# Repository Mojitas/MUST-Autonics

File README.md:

# Main repository for: MUST-Autonics 

## Sub-project VT1: Testbench

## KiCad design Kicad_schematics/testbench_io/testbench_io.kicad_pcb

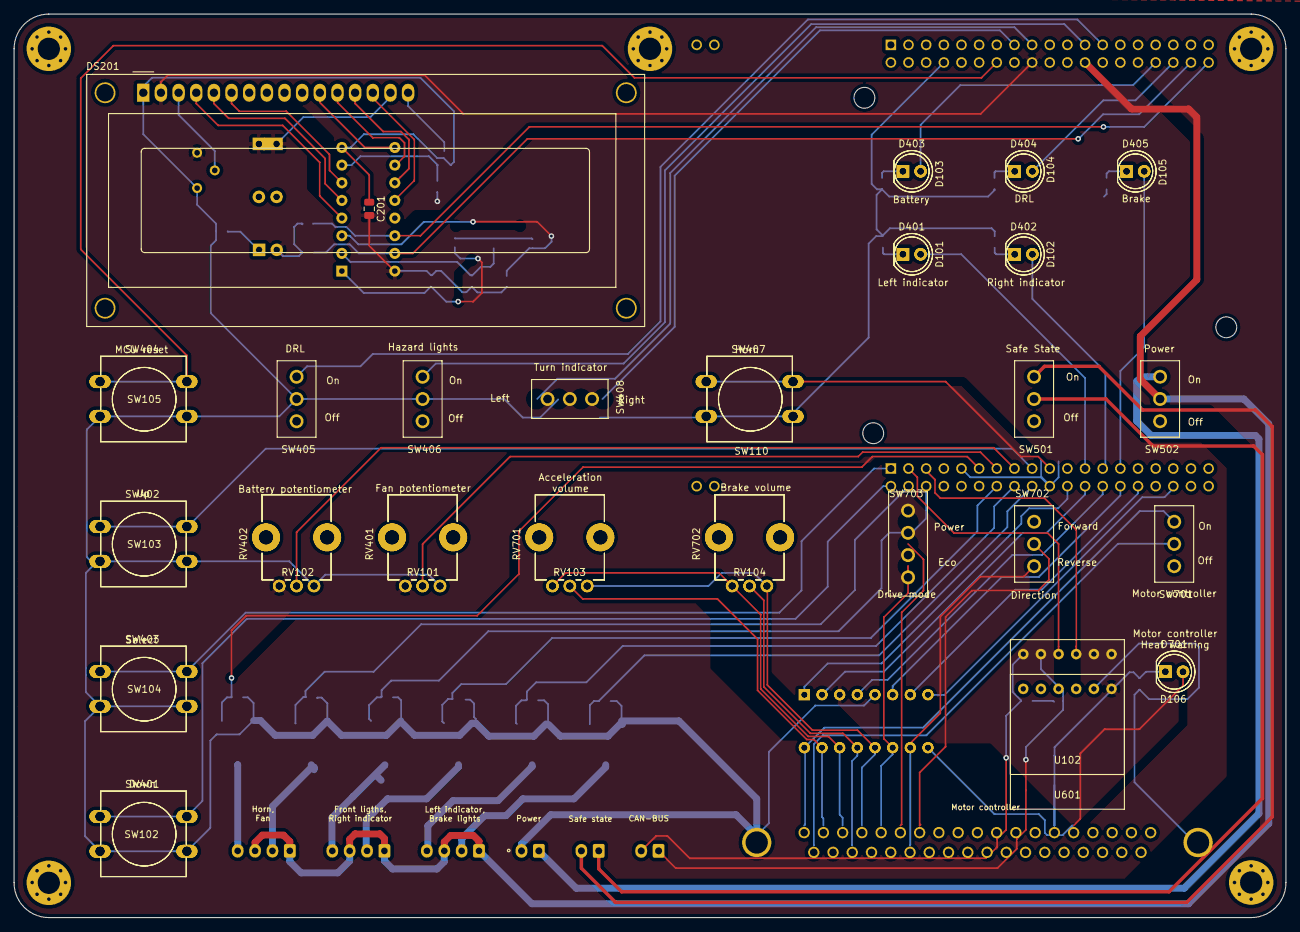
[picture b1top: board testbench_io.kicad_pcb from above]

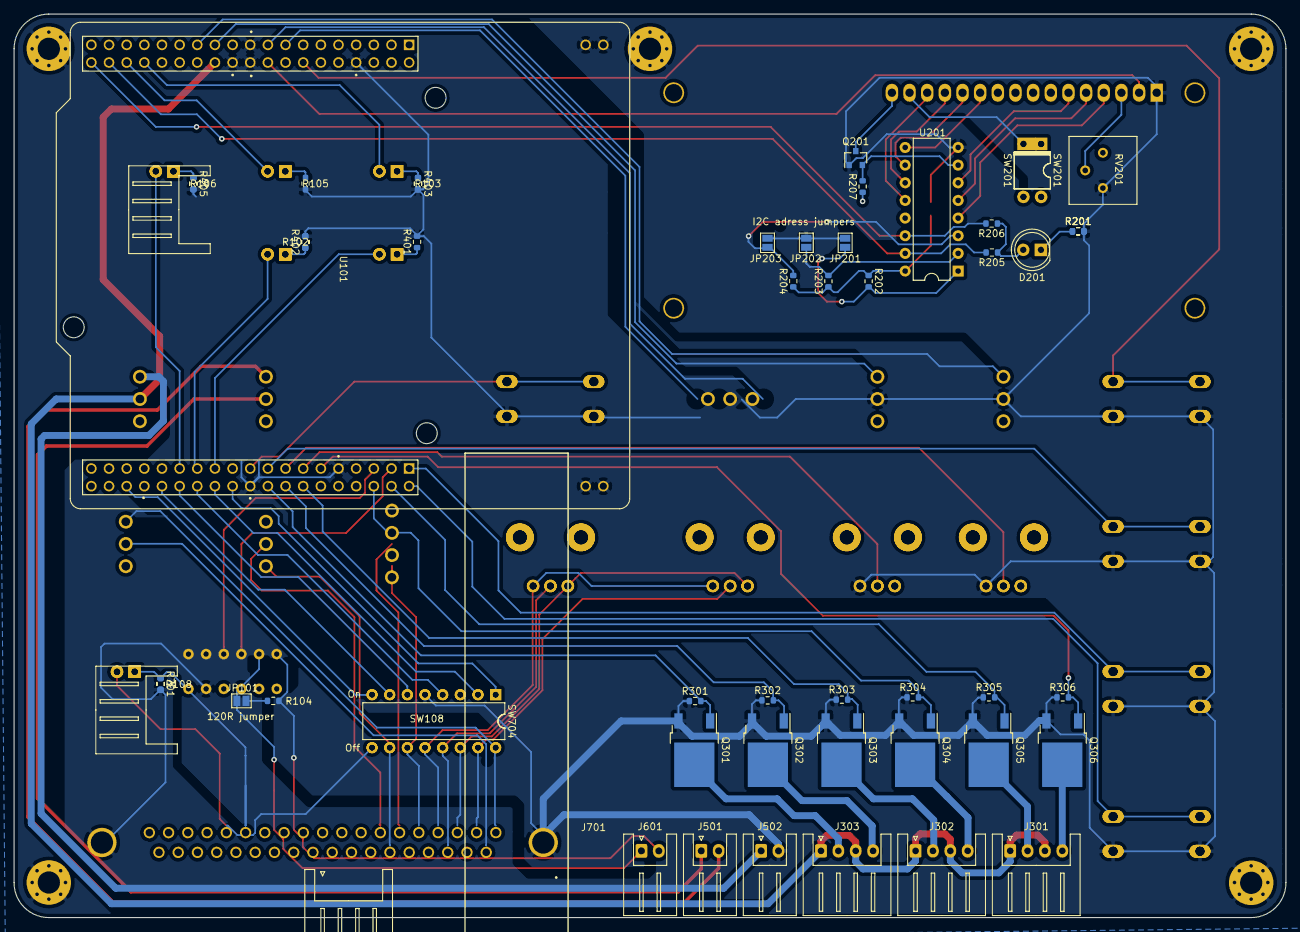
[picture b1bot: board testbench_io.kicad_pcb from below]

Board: 2 copper layers, 183.0 x 130.0 mm, 98 parts (51 on the bottom side), 87 nets.

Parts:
C201: 100n; C_0805_2012Metric
D101, D102, D103, D104, D105, D106, D201, D401, D402, D403, D404, D405, D701: LED; LED_D5.0mm
DS201: WC1602A
H101, H102, H103, H104, H105: MountingHole_Pad; MountingHole_3.2mm_M3_Pad_Via
J301, J302, J303: Conn_01x04; JST_XH_S4B-XH-A_1x04_P2.50mm_Horizontal
J501, J502, J601: Conn_01x02; JST_XH_S2B-XH-A_1x02_P2.50mm_Horizontal
J701: DB37_Male_MountingHoles; Wurth_Dsub_37_angled_male_8.08mm
JP101, JP201, JP202, JP203: SolderJumper_2_Open; SolderJumper-2_P1.3mm_Open_Pad1.0x1.5mm
Q201: 2N3904; SOT-23
Q301, Q302, Q303, Q304, Q305, Q306: IPD50R380CE; TO-252-2
R102, R103, R105, R106, R108, R305, R306, R401, R402, R403, R405, R701: R_Small; R_0603_1608Metric
R104: 120; R_0603_1608Metric
R201, R201#2: 1k; R_0603_1608Metric
R202, R203, R204, R301, R302, R303: 10k; R_0603_1608Metric
R205, R206, R207: 4.7; R_0603_1608Metric
R304: 100k; R_0603_1608Metric
RV101, RV102, RV103, RV104, RV401, RV402, RV701, RV702: R_POT; Potentiometer_Bourns_PTV09A-1_Single_Vertical
RV201: 10k; Potentiometer_Bourns_3386P_Vertical
SW102, SW103, SW104, SW105, SW110, SW401, SW402, SW403, SW404, SW407: SW_Push; SW_PUSH-12mm
SW108, SW704: SW_DIP_x08; DIP-16_W7.62mm
SW201: SW_DIP_x01; DIP-4_W7.62mm
SW201#2: SW_DIP_x01; Vishay_HVM-DIP-3_W7.62mm
SW405, SW406, SW501, SW502, SW701, SW702, SW703: SW_SPST; MFP120
SW408: SW_DPDT_x2; MFP130
U101: NUCLEO64-F476RG; MODULE_NUCLEO-F476RG
U102, U601: CJMCU_MCP2551; CJMCU_2551
U201: PCF8574AN; DIP-16_W7.62mm

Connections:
/Acc_vol: SW108.2, SW704.2, U101.62
/Battery_LED: D103.2, D403.2, U101.32
/Battery_pot: RV102.2, RV402.2, U101.53
/Brake_LED: D105.2, D405.2, U101.65
/Brake_acti: Q301.1, R301.2, U101.54
/Brake_vol: SW108.4, SW704.4, U101.64
/CAN/CAN_N: J601.1, R701.1, U601.6
/CAN/CAN_P: J601.2, R701.2, U601.5
/CRX: U101.41, U102.4, U601.4
/CTX: U101.43, U102.3, U601.3
/DRL_LED: D104.2, D404.2, U101.34
/DRL_sw: SW405.1, U101.25
/Down: SW102.1, SW401.1, U101.40
/F-R_sw: SW108.7, SW704.7, U101.68
/Fan_pot: RV101.2, RV401.2, U101.51
/Fan_pwm: Q305.1, R305.2, U101.42
/Front_acti: Q304.1, R304.2, U101.44
/HL_sw: SW406.1, U101.23
/Horn_acti: Q306.1, R306.2, U101.49
/Horn_sw: SW110.1, SW407.1, U101.57
/LCD_I2C/DB4: DS201.11, U201.9
/LCD_I2C/DB5: DS201.12, U201.10
/LCD_I2C/DB6: DS201.13, U201.11
/LCD_I2C/DB7: DS201.14, U201.12
/LCD_I2C/E: DS201.6, U201.6
/LCD_I2C/LED_(+): DS201.15, SW201.2, SW201#2.2
/LCD_I2C/LED_(-): DS201.16, Q201.3
/LCD_I2C/RS: DS201.4, U201.4
/LCD_I2C/RW: DS201.5, U201.5
/LCD_I2C/pot_brightness: DS201.3, RV201.2
/Left_LED: D101.2, D401.2, U101.61
/Left_acti: Q302.1, R302.2, U101.52
/Left_sw: SW703.1, U101.17
/MC_LED: SW108.8, SW704.8, U101.72
/MC_sw: SW108.1, SW704.1, U101.60
/Motor_controller/TRM_01: J701.1, SW701.1, SW704.16
/Motor_controller/TRM_02: J701.2, RV701.2, SW704.15
/Motor_controller/TRM_05: J701.5, SW704.11
/Motor_controller/TRM_14: D701.1, J701.14
/Motor_controller/TRM_15: D701.2, J701.15, SW704.9
/Motor_controller/TRM_20: J701.20, SW701.2
/Motor_controller/TRM_22: J701.22, RV702.2, SW704.13
/Motor_controller/TRM_25: J701.25, SW704.10
/P-E_sw: SW108.6, SW704.6, U101.66
/Reset: SW105.1, SW404.1, U101.14
/Right_LED: D102.2, D402.2, U101.63
/Right_acti: Q303.1, R303.2, U101.50
/Right_sw: SW703.3, U101.15
/SCL: R206.2, U101.38, U201.14
/SDA: R205.2, U101.36, U201.15
/Select: SW104.1, SW403.1, U101.39
/Solar_lights/Brake_lights_VSS: J303.2, Q301.2
/Solar_lights/Fan_VSS: J301.2, Q305.2
/Solar_lights/Front_lights_VSS: J302.4, Q304.2
/Solar_lights/Horn_VSS: J301.4, Q306.2
/Solar_lights/Left_indicator_VSS: J303.4, Q302.2
/Solar_lights/Right_indicator_VSS: J302.2, Q303.2
/TRM_02: RV103.2, SW108.15
/TRM_05: SW108.11, SW408.1
/TRM_14: D106.1, R108.1
/TRM_15: D106.2, SW108.9
/TRM_22: RV104.2, SW108.13
/TRM_25: SW108.10, SW501.1
/Up: SW103.1, SW402.1, U101.55
GND: C201.1, DS201.1, H101.1, H102.1, H103.1, H104.1, H105.1, J502.2, J701.0, JP201.2, JP202.2, JP203.2, Q201.1, Q301.3, Q302.3, Q303.3, Q304.3, Q305.3, Q306.3, R102.2, R103.2, R105.2, R106.2, R108.2, R201.2, R201#2.2, R301.1, R302.1, R303.1, R304.1, R305.1, R306.1, R401.2, R402.2, R403.2, R405.2, RV101.1, RV102.1, RV201.3, RV401.1, RV402.1, SW102.2, SW103.2, SW104.2, SW105.2, SW108.5, SW110.2, SW401.2, SW402.2, SW403.2, SW404.2, SW405.2, SW406.2, SW407.2, SW703.2, SW703.4, SW704.5, U101.8, U101.19, U101.20, U101.22, U101.47, U101.58, U101.77, U101.78, U101.79, U101.80, U102.2, U201.8, U601.2
MCU_5V: C201.2, D201.2, DS201.2, R202.1, R203.1, R204.1, R205.1, R206.1, R207.1, RV101.3, RV102.3, RV201.1, RV401.3, RV402.3, SW108.3, SW201.1, SW201#2.1, SW704.3, U101.18, U102.1, U201.16, U601.1
unnamed: D101.1, R201.1
unnamed: D102.1, R102.1
unnamed: D103.1, R103.1
unnamed: D104.1, R105.1
unnamed: D105.1, R106.1
unnamed: D201.1, R201#2.1
unnamed: D401.1, R401.1
unnamed: D402.1, R402.1
unnamed: D403.1, R403.1
unnamed: D404.1, R405.1
unnamed: JP101.1, U102.5
unnamed: R104.1, U102.6
unnamed: JP101.2, R104.2
unnamed: JP201.1, R202.2, U201.1
unnamed: JP202.1, R203.2, U201.2
unnamed: JP203.1, R204.2, U201.3
unnamed: Q201.2, R207.2, U201.7
TRM_GND: J701.4, J701.21, RV103.1, RV104.1, RV701.1, RV702.1, SW108.12, SW704.12
TRM_VDD: J701.3, J701.23, RV103.3, RV104.3, RV701.3, RV702.3, SW108.14, SW704.14
VDD_MCU: J301.1, J301.3, J302.1, J302.3, J303.1, J303.3, SW502.2, U101.24
V_external: J502.1, SW502.1

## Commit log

2020-07-11 Dummy plots
2020-07-11 Removed upload
2020-08-21 Added submodules for weatherlogging
2020-08-21 Removed submodule weatherLogging
2020-08-22 Squashed 'weatherLogging/' content from commit 941f80c
    git-subtree-dir: weatherLogging
    git-subtree-split: 941f80c710dfb7f4f9947b6ccba2ac2a1151ddca
2020-08-22 Removed weatherLogging subtree
2020-08-22 Added weatherLogging subtree
2020-09-23 Added HowToRDP for a remote connection
2020-09-30 Important update in HowToRDP
2020-11-18 Added a new cleaner battery schematics
2020-11-19 Added folder for blockdiagrams via git
2020-11-19 Added Low_voltage_diagram.drawio
2020-11-19 update Low_voltage_diagram
2020-11-19 Delete Untitled Diagram.drawio
    Removed empty file
2020-11-19 Added High_voltage_diagram
2020-11-19 Update High_voltage_diagram
2020-11-19 Added Pwr_dist_design
2020-11-19 Rename Pwr_dist_design to Cable channels & component placements
2020-11-19 Update Cable channels & component placements
2020-11-20 Added PDB.drawio
2020-11-20 Added nucleo_motherboard.drawio
2020-11-20 Added Battery
2020-11-20 Update Battery
2020-11-24 Added Dashboard
2020-11-24 Update Dashboard
2020-11-24 New projects
2020-12-03 Added folder
2020-12-03 Added my Local Nucleo Projects
2020-12-03 Create gitignore
2020-12-03 Removed .metadata
2020-12-03 Mathias code merged with project
2020-12-10 Added V2V folder with flow-chart diagrams and block diagrams over communication
2020-12-10 Added logs to the structure
2020-12-10 Added folders and temporary readme files that will be updated as project progresses
2020-12-10 Added links to the different diagrams files
2020-12-13 Added logger_nRF52840
2020-12-14 Implemented working version with FreeRTOS
2020-12-14 Receiver now has LCD Support
2020-12-15 Two threads implemented, none writes to file, and none writes to stdout, main can write but only in the end therefore making it a one thread program which is inefficient for detecting errors
2020-12-16 Added testbench_io
2020-12-16 Update testbench_io
2020-12-17 Added Copy of TestBenchFlowChartSW.xml
2020-12-17 Added Untitled Diagram.drawio
2020-12-17 Updated Comments
2020-12-17 Added TestBenchFlowChart.drawio
2020-12-17 Removed Misstakes...
2020-12-17 Diagrams
2020-12-17 Updated diagrams
2020-12-17 Added a diagram to README.md
2020-12-17 Updated TestBenchFlowChart
2020-12-17 Regex strings implemented as well as problems fixed
2020-12-21 updated battery schematics
2021-01-04 Fixed File extention
2021-01-04 Updated Test Bench Flow Chart
2021-01-04 Updated Block diagrams\TestBenchFlowChart.drawio
2021-01-04 reorganized and put all kicad schematics in one folder
2021-01-05 Added Test Bench Design to Git
2021-01-07 Merging so that everyone can see the figures. (#56)
    * Added logs to the structure
    * Added folders and temporary readme files that will be updated as project progresses
    * Added links to the different diagrams files
    * Update README.md
    * Updated README
    * Added logger_nRF52840
2021-01-08 Updatedf Block diagrams\TestBenchFlowChart.drawio
2021-01-08 Initiated Nucleo test bench interface project
2021-01-08 Created branch and added sensor code
2021-01-08 Added printing and fixed stack issue
2021-01-11 Updated project README file
2021-01-11 Added code for receiving device
2021-01-11 Logger updated
2021-01-13 added hierarchical sheets
2021-01-13 new branch
2021-01-14 Removed duplicates
    Orginisation of files
2021-01-15 Structure change
2021-01-15 Moved main.cpp to main_old.cpp and wrote a new main which will be used together with the new modular structure
2021-01-18 Added core functionality
2021-01-18 Removed some useless stuff
2021-01-18 Added footprints
2021-01-18 Added OS Tasks
2021-01-18 Started with layout
2021-01-19 Added some stuff
2021-01-19 IDE changed a line...
2021-01-19 Added more comments
2021-01-19 Added New Branch
2021-01-19 Added more functions
2021-01-19 Added LCD stuff
2021-01-19 Updated gitignore
2021-01-19 added gitignore
2021-01-19 Added Comments
2021-01-19 Updated Some LCD stuff
2021-01-19 Renamed central to template for programming, and added some code written for sender
2021-01-19 Pcb-layout is on the way
2021-01-20 stuff
2021-01-20 arduino stuff
2021-01-20 Added ToggleLED and button functions
2021-01-20 Added Interrupts and interrupt handlers
2021-01-21 Added Switches and SwitchStateChanged function
2021-01-21 Added Blink Left/Right with timer interrupts
2021-01-22 Updated with classes in sensor and battery, restructured a test file and configured doxygen for generation of documentation files
2021-01-22 Fixed timer callback and organised some code
2021-01-22 Added some more Switches and LED stuff
2021-01-22 Added debug stuff for switches
2021-01-23 Added some gitignores that removes .DS_Store files that macOS creates.
2021-01-23 Changes in structure
    A class has been added, as well as events and some other necessary functions.
2021-01-25 Routing done and power planes added
2021-01-25 Removed redundant tracks
2021-01-25 Added some final text about external connectors
2021-01-26 Added pullups and fixed warnings
2021-01-26 Added Cruise Controll Task
2021-01-26 Updated sender
2021-01-26 Change some header includes and some code in files to only do whats necessary
2021-01-26 Started working on receiver to lessen the implementation time
2021-01-26 herp di derp
    Daniel belives in himself...
2021-01-28 Fixed some footprints
2021-01-28 Fixed some final stuff
2021-01-28 Out with the old code and in with the new
    Found a link to an example that worked, took it and modified it with the code that I had written. Now the two nrf52840 development kits are connecting to each other and setting 8 symbols per bit as o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
2021-01-28 Made the power planes nicer.
2021-01-30 Updaetd code for both sender and receiver
2021-02-01 Implemented and Optimized LCD Menu
2021-02-01 Change of connector
    Changed a connector that wasn't available
2021-02-02 Some minor fixes and changes
2021-02-02 Edited some footprints to cheaper ones.
2021-02-02 Added ADC functionality to testbench userinterface
2021-02-02 And actually committed the changes...
2021-02-02 Added fixed lengths for each LCD row
2021-02-04 Changed source files, sender now periodically advertises data. Receiver does not receive.
2021-02-05 Fixed gerbers
2021-02-05 Cleaning up some
2021-02-05 Removing some stuff
2021-02-05 Check to see if .bak files follow
2021-02-05 check if bak is ignored
2021-02-05 updated ignore
2021-02-05 herp di derp
2021-02-05 Trying to get the git ig to work
2021-02-05 herp
2021-02-05 Revert "Trying to get the git ig to work"
    This reverts commit a2b1c48e4a7a630b46048bd5de177741188d3aaa.
2021-02-05 test
2021-02-12 Moved old into TODO folder and put new code in embedded-code folder
2021-02-16 Updated code and added config file for the two nRF radio devices. Added code for a nucleo which contains code for both SPI and SD card. The nRF also contains SPI and SD Card as well as BLE. And final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
2021-02-17 PCB sent to board house
2021-02-17 TODOs added in main.cpp, two places in the code has them, one chunk in the beginning and another further down. Those are the places that needs SPI implementation. First one is the SPI definition, as 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
2021-02-19 Sensor Trancive
2021-02-20 Updated code with comments that follow doxygen style on commenting, for generating beautiful output if we need to generate HTML or LaTeX manual based on code.
2021-02-20 Updated with more comments
2021-02-20 fixed shit
2021-03-04 Fixed text menu text formatting
2021-03-12 Testing acces token
2021-03-14 Added Testbench_IO_component_blockdiagram
2021-03-14 Update Testbench_IO_component_blockdiagram
2021-03-18 fixes
2021-03-23 CAN Baudrate fix
2021-03-23 Total derp fixed
2021-03-26 Attempt to fix can bus
2021-03-26 Updated CAN sheet to ethernet interface
2021-04-08 Updated git ignore
2021-04-08 Uploaded Fusion 360 CAD files
2021-06-15 Added documentation
